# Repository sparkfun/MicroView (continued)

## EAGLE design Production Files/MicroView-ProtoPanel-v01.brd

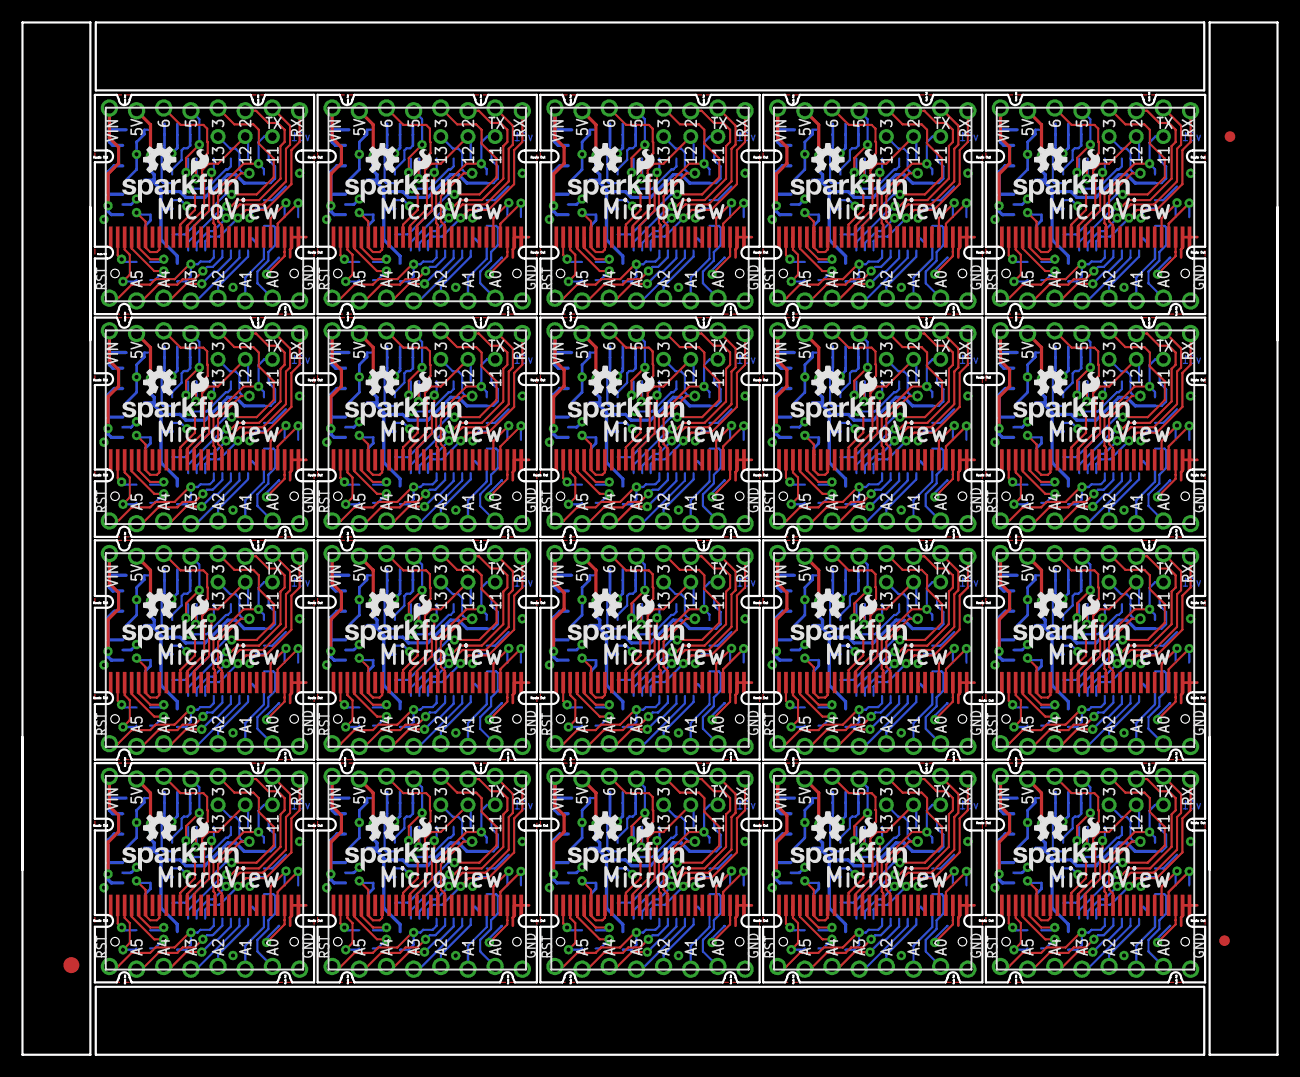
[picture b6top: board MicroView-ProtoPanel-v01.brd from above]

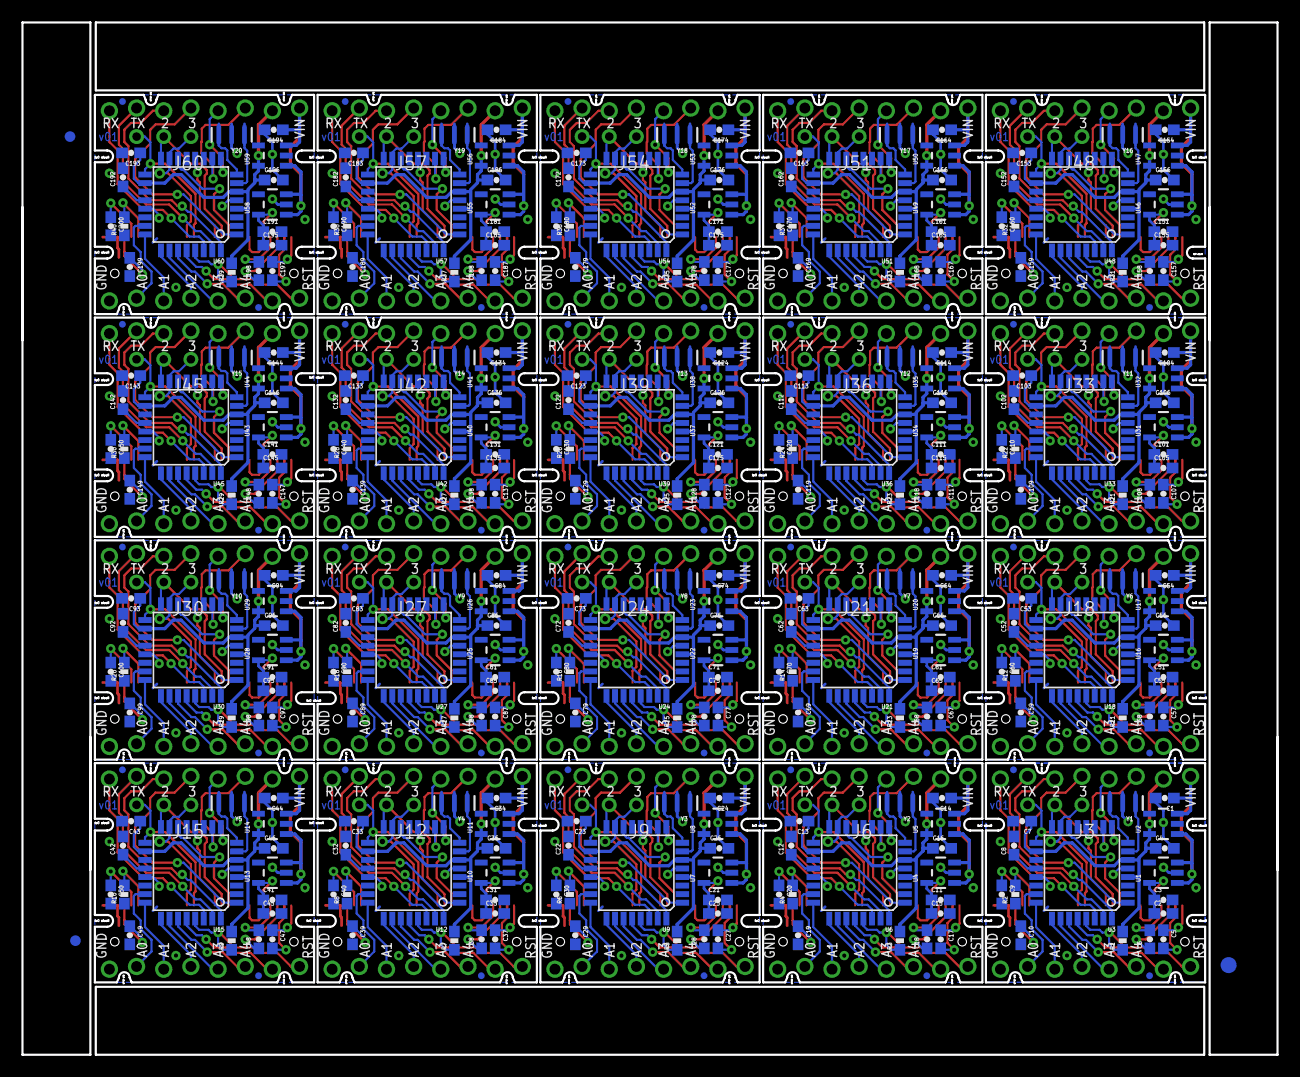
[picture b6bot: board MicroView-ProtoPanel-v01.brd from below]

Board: 2 copper layers, 117.3 x 96.5 mm, 486 parts (383 on the bottom side), 640 nets.

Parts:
C1, C2, C4, C5, C6, C14, C15, C16, C17, C18, C24, C25, C26, C27, C28, C34, C35, C36, C37, C38, C44, C45, C46, C47, C48, C54, C55, C56, C57, C58, C64, C65, C66, C67, C68, C74, C75, C76, C77, C78, C84, C85, C86, C87, C88, C94, C95, C96, C97, C98, C104, C105, C106, C107, C108, C114, C115, C116, C117, C118, C124, C125, C126, C127, C128, C134, C135, C136, C137, C138, C144, C145, C146, C147, C148, C154, C155, C156, C157, C158, C164, C165, C166, C167, C168, C174, C175, C176, C177, C178, C184, C185, C186, C187, C188, C194, C195, C196, C197, C198: 1.0uF; 0603-CAP
C3, C7, C8, C11, C12, C13, C21, C22, C23, C31, C32, C33, C41, C42, C43, C51, C52, C53, C61, C62, C63, C71, C72, C73, C81, C82, C83, C91, C92, C93, C101, C102, C103, C111, C112, C113, C121, C122, C123, C131, C132, C133, C141, C142, C143, C151, C152, C153, C161, C162, C163, C171, C172, C173, C181, C182, C183, C191, C192, C193: 0.1uF; 0603-CAP
C9, C10, C19, C20, C29, C30, C39, C40, C49, C50, C59, C60, C69, C70, C79, C80, C89, C90, C99, C100, C109, C110, C119, C120, C129, C130, C139, C140, C149, C150, C159, C160, C169, C170, C179, C180, C189, C190, C199, C200: 2.2uF; 0603-CAP
E$1, E$2: FIDUCIAL-1.5X3
E$3, E$4, E$5, E$6: FIDUCIAL-1X2
FID1, FID2, FID3, FID4, FID5, FID6, FID7, FID8, FID9, FID10, FID11, FID12, FID13, FID14, FID15, FID16, FID17, FID18, FID19, FID20, FID21, FID22, FID23, FID24, FID25, FID26, FID27, FID28, FID29, FID30, FID31, FID32, FID33, FID34, FID35, FID36, FID37, FID38, FID39, FID40: FIDUCIALUFIDUCIAL; MICRO-FIDUCIAL
J1, J5, J8, J11, J14, J17, J20, J23, J26, J29, J32, J35, J38, J41, J44, J47, J50, J53, J56, J59: OLED_SCREEN; OLED-SCREEN
J2, J4, J7, J10, J13, J16, J19, J22, J25, J28, J31, J34, J37, J40, J43, J46, J49, J52, J55, J58: MICROVIEW-16; MV-DIP16
J3, J6, J9, J12, J15, J18, J21, J24, J27, J30, J33, J36, J39, J42, J45, J48, J51, J54, J57, J60: M03NS_SLIM; 1X03_NS_SLIM
LOGO1, LOGO2, LOGO5, LOGO7, LOGO9, LOGO11, LOGO13, LOGO15, LOGO17, LOGO19, LOGO21, LOGO23, LOGO25, LOGO27, LOGO29, LOGO31, LOGO33, LOGO35, LOGO37, LOGO39: OSHW-LOGOS; OSHW-LOGO-S
LOGO3, LOGO4, LOGO6, LOGO8, LOGO10, LOGO12, LOGO14, LOGO16, LOGO18, LOGO20, LOGO22, LOGO24, LOGO26, LOGO28, LOGO30, LOGO32, LOGO34, LOGO36, LOGO38, LOGO40: SFE_LOGO_NAME_FLAME.1_INCH; SFE_LOGO_NAME_FLAME_.1
OLED1, OLED2, OLED3, OLED4, OLED5, OLED6, OLED7, OLED8, OLED9, OLED10, OLED11, OLED12, OLED13, OLED14, OLED15, OLED16, OLED17, OLED18, OLED19, OLED20: OLED0.66; OLED-0.66-64X48
R1, R3, R5, R7, R9, R11, R13, R15, R17, R19, R21, R23, R25, R27, R29, R31, R33, R35, R37, R39: 10K; 0603-RES
R2, R4, R6, R8, R10, R12, R14, R16, R18, R20, R22, R24, R26, R28, R30, R32, R34, R36, R38, R40: 390k; 0603-RES
U1, U4, U7, U10, U13, U16, U19, U22, U25, U28, U31, U34, U37, U40, U43, U46, U49, U52, U55, U58: MIC5205 3.3V; SOT23-5
U2, U5, U8, U11, U14, U17, U20, U23, U26, U29, U32, U35, U38, U41, U44, U47, U50, U53, U56, U59: SPX3819M5-L-5-0; SOT23-5
U3, U6, U9, U12, U15, U18, U21, U24, U27, U30, U33, U36, U39, U42, U45, U48, U51, U54, U57, U60: ATMEGA328P; TQFP32-08
Y1, Y2, Y3, Y4, Y5, Y6, Y7, Y8, Y9, Y10, Y11, Y12, Y13, Y14, Y15, Y16, Y17, Y18, Y19, Y20: 16MHz; RESONATOR-SMD

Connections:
3.3V: C2.1, C3.1, OLED1.6, OLED1.8, U1.5
3.3V1: C11.1, C15.1, OLED2.6, OLED2.8, U4.5
3.3V2: C21.1, C25.1, OLED3.6, OLED3.8, U7.5
3.3V3: C31.1, C35.1, OLED4.6, OLED4.8, U10.5
3.3V4: C41.1, C45.1, OLED5.6, OLED5.8, U13.5
3.3V5: C51.1, C55.1, OLED6.6, OLED6.8, U16.5
3.3V6: C61.1, C65.1, OLED7.6, OLED7.8, U19.5
3.3V7: C71.1, C75.1, OLED8.6, OLED8.8, U22.5
3.3V8: C81.1, C85.1, OLED9.6, OLED9.8, U25.5
3.3V9: C91.1, C95.1, OLED10.6, OLED10.8, U28.5
3.3V10: C101.1, C105.1, OLED11.6, OLED11.8, U31.5
3.3V11: C111.1, C115.1, OLED12.6, OLED12.8, U34.5
3.3V12: C121.1, C125.1, OLED13.6, OLED13.8, U37.5
3.3V13: C131.1, C135.1, OLED14.6, OLED14.8, U40.5
3.3V14: C141.1, C145.1, OLED15.6, OLED15.8, U43.5
3.3V15: C151.1, C155.1, OLED16.6, OLED16.8, U46.5
3.3V16: C161.1, C165.1, OLED17.6, OLED17.8, U49.5
3.3V17: C171.1, C175.1, OLED18.6, OLED18.8, U52.5
3.3V18: C181.1, C185.1, OLED19.6, OLED19.8, U55.5
3.3V19: C191.1, C195.1, OLED20.6, OLED20.8, U58.5
5V: C4.1, C7.1, J2.15, R1.2, U2.5, U3.4, U3.6, U3.18
5V1: C13.1, C16.1, J4.15, R3.2, U5.5, U6.4, U6.6, U6.18
5V2: C23.1, C26.1, J7.15, R5.2, U8.5, U9.4, U9.6, U9.18
5V3: C33.1, C36.1, J10.15, R7.2, U11.5, U12.4, U12.6, U12.18
5V4: C43.1, C46.1, J13.15, R9.2, U14.5, U15.4, U15.6, U15.18
5V5: C53.1, C56.1, J16.15, R11.2, U17.5, U18.4, U18.6, U18.18
5V6: C63.1, C66.1, J19.15, R13.2, U20.5, U21.4, U21.6, U21.18
5V7: C73.1, C76.1, J22.15, R15.2, U23.5, U24.4, U24.6, U24.18
5V8: C83.1, C86.1, J25.15, R17.2, U26.5, U27.4, U27.6, U27.18
5V9: C93.1, C96.1, J28.15, R19.2, U29.5, U30.4, U30.6, U30.18
5V10: C103.1, C106.1, J31.15, R21.2, U32.5, U33.4, U33.6, U33.18
5V11: C113.1, C116.1, J34.15, R23.2, U35.5, U36.4, U36.6, U36.18
5V12: C123.1, C126.1, J37.15, R25.2, U38.5, U39.4, U39.6, U39.18
5V13: C133.1, C136.1, J40.15, R27.2, U41.5, U42.4, U42.6, U42.18
5V14: C143.1, C146.1, J43.15, R29.2, U44.5, U45.4, U45.6, U45.18
5V15: C153.1, C156.1, J46.15, R31.2, U47.5, U48.4, U48.6, U48.18
5V16: C163.1, C166.1, J49.15, R33.2, U50.5, U51.4, U51.6, U51.18
5V17: C173.1, C176.1, J52.15, R35.2, U53.5, U54.4, U54.6, U54.18
5V18: C183.1, C186.1, J55.15, R37.2, U56.5, U57.4, U57.6, U57.18
5V19: C193.1, C196.1, J58.15, R39.2, U59.5, U60.4, U60.6, U60.18
A0: J2.7, U3.23
A1: J2.6, U3.24
A2: J2.5, U3.25
A3: J2.4, U3.26
A4: J2.3, U3.27
A5: J2.2, U3.28
A6: J4.7, U6.23
A7: J4.6, U6.24
A8: J4.5, U6.25
A9: J4.4, U6.26
A10: J4.3, U6.27
A11: J4.2, U6.28
A12: J7.7, U9.23
A13: J7.6, U9.24
A14: J7.5, U9.25
A15: J7.4, U9.26
A16: J7.3, U9.27
A17: J7.2, U9.28
A18: J10.7, U12.23
A19: J10.6, U12.24
A20: J10.5, U12.25
A21: J10.4, U12.26
A22: J10.3, U12.27
A23: J10.2, U12.28
A24: J13.7, U15.23
A25: J13.6, U15.24
A26: J13.5, U15.25
A27: J13.4, U15.26
A28: J13.3, U15.27
A29: J13.2, U15.28
A30: J16.7, U18.23
A31: J16.6, U18.24
A32: J16.5, U18.25
A33: J16.4, U18.26
A34: J16.3, U18.27
A35: J16.2, U18.28
A36: J19.7, U21.23
A37: J19.6, U21.24
A38: J19.5, U21.25
A39: J19.4, U21.26
A40: J19.3, U21.27
A41: J19.2, U21.28
A42: J22.7, U24.23
A43: J22.6, U24.24
A44: J22.5, U24.25
A45: J22.4, U24.26
A46: J22.3, U24.27
A47: J22.2, U24.28
A48: J25.7, U27.23
A49: J25.6, U27.24
A50: J25.5, U27.25
A51: J25.4, U27.26
A52: J25.3, U27.27
A53: J25.2, U27.28
A54: J28.7, U30.23
A55: J28.6, U30.24
A56: J28.5, U30.25
A57: J28.4, U30.26
A58: J28.3, U30.27
A59: J28.2, U30.28
A60: J31.7, U33.23
A61: J31.6, U33.24
A62: J31.5, U33.25
A63: J31.4, U33.26
A64: J31.3, U33.27
A65: J31.2, U33.28
A66: J34.7, U36.23
A67: J34.6, U36.24
A68: J34.5, U36.25
A69: J34.4, U36.26
A70: J34.3, U36.27
A71: J34.2, U36.28
A72: J37.7, U39.23
A73: J37.6, U39.24
A74: J37.5, U39.25
A75: J37.4, U39.26
A76: J37.3, U39.27
A77: J37.2, U39.28
A78: J40.7, U42.23
A79: J40.6, U42.24
A80: J40.5, U42.25
A81: J40.4, U42.26
A82: J40.3, U42.27
A83: J40.2, U42.28
A84: J43.7, U45.23
A85: J43.6, U45.24
A86: J43.5, U45.25
A87: J43.4, U45.26
A88: J43.3, U45.27
A89: J43.2, U45.28
A90: J46.7, U48.23
A91: J46.6, U48.24
A92: J46.5, U48.25
A93: J46.4, U48.26
A94: J46.3, U48.27
A95: J46.2, U48.28
A96: J49.7, U51.23
A97: J49.6, U51.24
A98: J49.5, U51.25
A99: J49.4, U51.26
A100: J49.3, U51.27
A101: J49.2, U51.28
A102: J52.7, U54.23
A103: J52.6, U54.24
A104: J52.5, U54.25
A105: J52.4, U54.26
A106: J52.3, U54.27
A107: J52.2, U54.28
A108: J55.7, U57.23
A109: J55.6, U57.24
A110: J55.5, U57.25
A111: J55.4, U57.26
A112: J55.3, U57.27
A113: J55.2, U57.28
A114: J58.7, U60.23
A115: J58.6, U60.24
A116: J58.5, U60.25
A117: J58.4, U60.26
A118: J58.3, U60.27
A119: J58.2, U60.28
C1N: C6.2, OLED1.5
C1N1: C18.2, OLED2.5
C1N2: C28.2, OLED3.5
C1N3: C38.2, OLED4.5
C1N4: C48.2, OLED5.5
C1N5: C58.2, OLED6.5
C1N6: C68.2, OLED7.5
C1N7: C78.2, OLED8.5
C1N8: C88.2, OLED9.5
C1N9: C98.2, OLED10.5
C1N10: C108.2, OLED11.5
C1N11: C118.2, OLED12.5
C1N12: C128.2, OLED13.5
C1N13: C138.2, OLED14.5
C1N14: C148.2, OLED15.5
C1N15: C158.2, OLED16.5
C1N16: C168.2, OLED17.5
C1N17: C178.2, OLED18.5
C1N18: C188.2, OLED19.5
C1N19: C198.2, OLED20.5
C1P: C6.1, OLED1.4
C1P1: C18.1, OLED2.4
C1P2: C28.1, OLED3.4
C1P3: C38.1, OLED4.4
C1P4: C48.1, OLED5.4
C1P5: C58.1, OLED6.4
C1P6: C68.1, OLED7.4
C1P7: C78.1, OLED8.4
C1P8: C88.1, OLED9.4
C1P9: C98.1, OLED10.4
C1P10: C108.1, OLED11.4
C1P11: C118.1, OLED12.4
C1P12: C128.1, OLED13.4
C1P13: C138.1, OLED14.4
C1P14: C148.1, OLED15.4
C1P15: C158.1, OLED16.4
C1P16: C168.1, OLED17.4
C1P17: C178.1, OLED18.4
C1P18: C188.1, OLED19.4
C1P19: C198.1, OLED20.4
C2N: C5.2, OLED1.3
C2N1: C17.2, OLED2.3
C2N2: C27.2, OLED3.3
C2N3: C37.2, OLED4.3
C2N4: C47.2, OLED5.3
C2N5: C57.2, OLED6.3
C2N6: C67.2, OLED7.3
C2N7: C77.2, OLED8.3
C2N8: C87.2, OLED9.3
C2N9: C97.2, OLED10.3
C2N10: C107.2, OLED11.3
C2N11: C117.2, OLED12.3
C2N12: C127.2, OLED13.3
C2N13: C137.2, OLED14.3
C2N14: C147.2, OLED15.3
C2N15: C157.2, OLED16.3
C2N16: C167.2, OLED17.3
C2N17: C177.2, OLED18.3
C2N18: C187.2, OLED19.3
C2N19: C197.2, OLED20.3
C2P: C5.1, OLED1.2
C2P1: C17.1, OLED2.2
C2P2: C27.1, OLED3.2
C2P3: C37.1, OLED4.2
C2P4: C47.1, OLED5.2
C2P5: C57.1, OLED6.2
C2P6: C67.1, OLED7.2
C2P7: C77.1, OLED8.2
C2P8: C87.1, OLED9.2
C2P9: C97.1, OLED10.2
C2P10: C107.1, OLED11.2
C2P11: C117.1, OLED12.2
C2P12: C127.1, OLED13.2
C2P13: C137.1, OLED14.2
C2P14: C147.1, OLED15.2
C2P15: C157.1, OLED16.2
C2P16: C167.1, OLED17.2
C2P17: C177.1, OLED18.2
C2P18: C187.1, OLED19.2
C2P19: C197.1, OLED20.2
D1: J4.11, U6.32
D2: J2.11, U3.32
D3: J2.12, U3.1
D4: J4.12, U6.1
D5: J2.13, U3.9
D6: J2.14, U3.10
D7: J4.13, U6.9
D8: J4.14, U6.10
D8/D!C!: OLED1.13, U3.12
D8/D!C!1: OLED2.13, U6.12
D8/D!C!2: OLED3.13, U9.12
D8/D!C!3: OLED4.13, U12.12
D8/D!C!4: OLED5.13, U15.12
D8/D!C!5: OLED6.13, U18.12
D8/D!C!6: OLED7.13, U21.12
D8/D!C!7: OLED8.13, U24.12
D8/D!C!8: OLED9.13, U27.12
D8/D!C!9: OLED10.13, U30.12
D8/D!C!10: OLED11.13, U33.12
D8/D!C!11: OLED12.13, U36.12
D8/D!C!12: OLED13.13, U39.12
D8/D!C!13: OLED14.13, U42.12
D8/D!C!14: OLED15.13, U45.12
D8/D!C!15: OLED16.13, U48.12
D8/D!C!16: OLED17.13, U51.12
D8/D!C!17: OLED18.13, U54.12
D8/D!C!18: OLED19.13, U57.12
D8/D!C!19: OLED20.13, U60.12
D9: J7.11, U9.32
D10: J7.12, U9.1
D10/SS: OLED1.11, U3.14
D10/SS1: OLED2.11, U6.14
D10/SS2: OLED3.11, U9.14
D10/SS3: OLED4.11, U12.14
D10/SS4: OLED5.11, U15.14
D10/SS5: OLED6.11, U18.14
D10/SS6: OLED7.11, U21.14
D10/SS7: OLED8.11, U24.14
D10/SS8: OLED9.11, U27.14
D10/SS9: OLED10.11, U30.14
D10/SS10: OLED11.11, U33.14
D10/SS11: OLED12.11, U36.14
D10/SS12: OLED13.11, U39.14
D10/SS13: OLED14.11, U42.14
D10/SS14: OLED15.11, U45.14
D10/SS15: OLED16.11, U48.14
D10/SS16: OLED17.11, U51.14
D10/SS17: OLED18.11, U54.14
D10/SS18: OLED19.11, U57.14
D10/SS19: OLED20.11, U60.14
D11: J7.13, U9.9
D11/MOSI: J3.1, OLED1.17, U3.15
D11/MOSI1: J6.1, OLED2.17, U6.15
D11/MOSI2: J9.1, OLED3.17, U9.15
D11/MOSI3: J12.1, OLED4.17, U12.15
D11/MOSI4: J15.1, OLED5.17, U15.15
D11/MOSI5: J18.1, OLED6.17, U18.15
D11/MOSI6: J21.1, OLED7.17, U21.15
D11/MOSI7: J24.1, OLED8.17, U24.15
D11/MOSI8: J27.1, OLED9.17, U27.15
D11/MOSI9: J30.1, OLED10.17, U30.15
D11/MOSI10: J33.1, OLED11.17, U33.15
D11/MOSI11: J36.1, OLED12.17, U36.15
D11/MOSI12: J39.1, OLED13.17, U39.15
D11/MOSI13: J42.1, OLED14.17, U42.15
D11/MOSI14: J45.1, OLED15.17, U45.15
D11/MOSI15: J48.1, OLED16.17, U48.15
D11/MOSI16: J51.1, OLED17.17, U51.15
D11/MOSI17: J54.1, OLED18.17, U54.15
D11/MOSI18: J57.1, OLED19.17, U57.15
D11/MOSI19: J60.1, OLED20.17, U60.15
D12: J7.14, U9.10
D12/MISO: J3.2, OLED1.12, U3.16
D12/MISO1: J6.2, OLED2.12, U6.16
D12/MISO2: J9.2, OLED3.12, U9.16
D12/MISO3: J12.2, OLED4.12, U12.16
D12/MISO4: J15.2, OLED5.12, U15.16
D12/MISO5: J18.2, OLED6.12, U18.16
D12/MISO6: J21.2, OLED7.12, U21.16
D12/MISO7: J24.2, OLED8.12, U24.16
D12/MISO8: J27.2, OLED9.12, U27.16
D12/MISO9: J30.2, OLED10.12, U30.16
D12/MISO10: J33.2, OLED11.12, U33.16
D12/MISO11: J36.2, OLED12.12, U36.16
D12/MISO12: J39.2, OLED13.12, U39.16
D12/MISO13: J42.2, OLED14.12, U42.16
D12/MISO14: J45.2, OLED15.12, U45.16
D12/MISO15: J48.2, OLED16.12, U48.16
D12/MISO16: J51.2, OLED17.12, U51.16
D12/MISO17: J54.2, OLED18.12, U54.16
D12/MISO18: J57.2, OLED19.12, U57.16
D12/MISO19: J60.2, OLED20.12, U60.16
D13: J10.11, U12.32
D13/SCK: J3.3, OLED1.16, U3.17
D13/SCK1: J6.3, OLED2.16, U6.17
D13/SCK2: J9.3, OLED3.16, U9.17
D13/SCK3: J12.3, OLED4.16, U12.17
D13/SCK4: J15.3, OLED5.16, U15.17
D13/SCK5: J18.3, OLED6.16, U18.17
D13/SCK6: J21.3, OLED7.16, U21.17
D13/SCK7: J24.3, OLED8.16, U24.17
D13/SCK8: J27.3, OLED9.16, U27.17
D13/SCK9: J30.3, OLED10.16, U30.17
D13/SCK10: J33.3, OLED11.16, U33.17
D13/SCK11: J36.3, OLED12.16, U36.17
D13/SCK12: J39.3, OLED13.16, U39.17
D13/SCK13: J42.3, OLED14.16, U42.17
D13/SCK14: J45.3, OLED15.16, U45.17
D13/SCK15: J48.3, OLED16.16, U48.17
D13/SCK16: J51.3, OLED17.16, U51.17
D13/SCK17: J54.3, OLED18.16, U54.17
D13/SCK18: J57.3, OLED19.16, U57.17
D13/SCK19: J60.3, OLED20.16, U60.17
D14: J10.12, U12.1
D15: J10.13, U12.9
D16: J10.14, U12.10
D17: J13.11, U15.32
D18: J13.12, U15.1
D19: J13.13, U15.9
D20: J13.14, U15.10
D21: J16.11, U18.32
D22: J16.12, U18.1
D23: J16.13, U18.9
D24: J16.14, U18.10
D25: J19.11, U21.32
D26: J19.12, U21.1
D27: J19.13, U21.9
D28: J19.14, U21.10
D29: J22.11, U24.32
D30: J22.12, U24.1
D31: J22.13, U24.9
D32: J22.14, U24.10
D33: J25.11, U27.32
D34: J25.12, U27.1
D35: J25.13, U27.9
D36: J25.14, U27.10
D37: J28.11, U30.32
D38: J28.12, U30.1
D39: J28.13, U30.9
D40: J28.14, U30.10
D41: J31.11, U33.32
D42: J31.12, U33.1
D43: J31.13, U33.9
D44: J31.14, U33.10
D45: J34.11, U36.32
D46: J34.12, U36.1
D47: J34.13, U36.9
D48: J34.14, U36.10
D49: J37.11, U39.32
D50: J37.12, U39.1
D51: J37.13, U39.9
D52: J37.14, U39.10
D53: J40.11, U42.32
D54: J40.12, U42.1
D55: J40.13, U42.9
D56: J40.14, U42.10
D57: J43.11, U45.32
D58: J43.12, U45.1
D59: J43.13, U45.9
D60: J43.14, U45.10
D61: J46.11, U48.32
D62: J46.12, U48.1
D63: J46.13, U48.9
D64: J46.14, U48.10
D65: J49.11, U51.32
D66: J49.12, U51.1
D67: J49.13, U51.9
D68: J49.14, U51.10
D69: J52.11, U54.32
D70: J52.12, U54.1
D71: J52.13, U54.9
D72: J52.14, U54.10
D73: J55.11, U57.32
D74: J55.12, U57.1
D75: J55.13, U57.9
D76: J55.14, U57.10
D77: J58.11, U60.32
D78: J58.12, U60.1
D79: J58.13, U60.9
D80: J58.14, U60.10
GND: C1.2, C2.2, C3.2, C4.2, C7.2, C8.2, C9.2, C10.2, J2.8, OLED1.1, OLED1.7, OLED1.9, OLED1.10, OLED1.27, OLED1.28, R2.1, U1.2, U2.2, U3.3, U3.5, U3.21, Y1.2
GND1: C11.2, C12.2, C13.2, C14.2, C15.2, C16.2, C19.2, C20.2, J4.8, OLED2.1, OLED2.7, OLED2.9, OLED2.10, OLED2.27, OLED2.28, R4.1, U4.2, U5.2, U6.3, U6.5, U6.21, Y2.2
GND2: C21.2, C22.2, C23.2, C24.2, C25.2, C26.2, C29.2, C30.2, J7.8, OLED3.1, OLED3.7, OLED3.9, OLED3.10, OLED3.27, OLED3.28, R6.1, U7.2, U8.2, U9.3, U9.5, U9.21, Y3.2
GND3: C31.2, C32.2, C33.2, C34.2, C35.2, C36.2, C39.2, C40.2, J10.8, OLED4.1, OLED4.7, OLED4.9, OLED4.10, OLED4.27, OLED4.28, R8.1, U10.2, U11.2, U12.3, U12.5, U12.21, Y4.2
GND4: C41.2, C42.2, C43.2, C44.2, C45.2, C46.2, C49.2, C50.2, J13.8, OLED5.1, OLED5.7, OLED5.9, OLED5.10, OLED5.27, OLED5.28, R10.1, U13.2, U14.2, U15.3, U15.5, U15.21, Y5.2
GND5: C51.2, C52.2, C53.2, C54.2, C55.2, C56.2, C59.2, C60.2, J16.8, OLED6.1, OLED6.7, OLED6.9, OLED6.10, OLED6.27, OLED6.28, R12.1, U16.2, U17.2, U18.3, U18.5, U18.21, Y6.2
GND6: C61.2, C62.2, C63.2, C64.2, C65.2, C66.2, C69.2, C70.2, J19.8, OLED7.1, OLED7.7, OLED7.9, OLED7.10, OLED7.27, OLED7.28, R14.1, U19.2, U20.2, U21.3, U21.5, U21.21, Y7.2
GND7: C71.2, C72.2, C73.2, C74.2, C75.2, C76.2, C79.2, C80.2, J22.8, OLED8.1, OLED8.7, OLED8.9, OLED8.10, OLED8.27, OLED8.28, R16.1, U22.2, U23.2, U24.3, U24.5, U24.21, Y8.2
GND8: C81.2, C82.2, C83.2, C84.2, C85.2, C86.2, C89.2, C90.2, J25.8, OLED9.1, OLED9.7, OLED9.9, OLED9.10, OLED9.27, OLED9.28, R18.1, U25.2, U26.2, U27.3, U27.5, U27.21, Y9.2
GND9: C91.2, C92.2, C93.2, C94.2, C95.2, C96.2, C99.2, C100.2, J28.8, OLED10.1, OLED10.7, OLED10.9, OLED10.10, OLED10.27, OLED10.28, R20.1, U28.2, U29.2, U30.3, U30.5, U30.21, Y10.2
GND10: C101.2, C102.2, C103.2, C104.2, C105.2, C106.2, C109.2, C110.2, J31.8, OLED11.1, OLED11.7, OLED11.9, OLED11.10, OLED11.27, OLED11.28, R22.1, U31.2, U32.2, U33.3, U33.5, U33.21, Y11.2
GND11: C111.2, C112.2, C113.2, C114.2, C115.2, C116.2, C119.2, C120.2, J34.8, OLED12.1, OLED12.7, OLED12.9, OLED12.10, OLED12.27, OLED12.28, R24.1, U34.2, U35.2, U36.3, U36.5, U36.21, Y12.2
GND12: C121.2, C122.2, C123.2, C124.2, C125.2, C126.2, C129.2, C130.2, J37.8, OLED13.1, OLED13.7, OLED13.9, OLED13.10, OLED13.27, OLED13.28, R26.1, U37.2, U38.2, U39.3, U39.5, U39.21, Y13.2
GND13: C131.2, C132.2, C133.2, C134.2, C135.2, C136.2, C139.2, C140.2, J40.8, OLED14.1, OLED14.7, OLED14.9, OLED14.10, OLED14.27, OLED14.28, R28.1, U40.2, U41.2, U42.3, U42.5, U42.21, Y14.2
GND14: C141.2, C142.2, C143.2, C144.2, C145.2, C146.2, C149.2, C150.2, J43.8, OLED15.1, OLED15.7, OLED15.9, OLED15.10, OLED15.27, OLED15.28, R30.1, U43.2, U44.2, U45.3, U45.5, U45.21, Y15.2
GND15: C151.2, C152.2, C153.2, C154.2, C155.2, C156.2, C159.2, C160.2, J46.8, OLED16.1, OLED16.7, OLED16.9, OLED16.10, OLED16.27, OLED16.28, R32.1, U46.2, U47.2, U48.3, U48.5, U48.21, Y16.2
GND16: C161.2, C162.2, C163.2, C164.2, C165.2, C166.2, C169.2, C170.2, J49.8, OLED17.1, OLED17.7, OLED17.9, OLED17.10, OLED17.27, OLED17.28, R34.1, U49.2, U50.2, U51.3, U51.5, U51.21, Y17.2
GND17: C171.2, C172.2, C173.2, C174.2, C175.2, C176.2, C179.2, C180.2, J52.8, OLED18.1, OLED18.7, OLED18.9, OLED18.10, OLED18.27, OLED18.28, R36.1, U52.2, U53.2, U54.3, U54.5, U54.21, Y18.2
GND18: C181.2, C182.2, C183.2, C184.2, C185.2, C186.2, C189.2, C190.2, J55.8, OLED19.1, OLED19.7, OLED19.9, OLED19.10, OLED19.27, OLED19.28, R38.1, U55.2, U56.2, U57.3, U57.5, U57.21, Y19.2
GND19: C191.2, C192.2, C193.2, C194.2, C195.2, C196.2, C199.2, C200.2, J58.8, OLED20.1, OLED20.7, OLED20.9, OLED20.10, OLED20.27, OLED20.28, R40.1, U58.2, U59.2, U60.3, U60.5, U60.21, Y20.2
unnamed: C10.1, OLED1.26
unnamed: C9.1, OLED1.25
unnamed: OLED1.24, R2.2
unnamed: C19.1, OLED2.26
unnamed: C20.1, OLED2.25
unnamed: OLED2.24, R4.2
unnamed: U6.7, Y2.1
unnamed: U3.7, Y1.1
unnamed: U3.8, Y1.3
unnamed: C8.1, U3.20
unnamed: U6.8, Y2.3
unnamed: C12.1, U6.20
unnamed: C29.1, OLED3.26
unnamed: C30.1, OLED3.25
unnamed: OLED3.24, R6.2
unnamed: U9.7, Y3.1
unnamed: U9.8, Y3.3
unnamed: C22.1, U9.20
unnamed: C39.1, OLED4.26
unnamed: C40.1, OLED4.25
unnamed: OLED4.24, R8.2
unnamed: U12.7, Y4.1
unnamed: U12.8, Y4.3
unnamed: C32.1, U12.20
unnamed: C49.1, OLED5.26
unnamed: C50.1, OLED5.25
unnamed: OLED5.24, R10.2
unnamed: U15.7, Y5.1
unnamed: U15.8, Y5.3
unnamed: C42.1, U15.20
unnamed: C59.1, OLED6.26
unnamed: C60.1, OLED6.25
unnamed: OLED6.24, R12.2
unnamed: U18.7, Y6.1
unnamed: U18.8, Y6.3
unnamed: C52.1, U18.20
unnamed: C69.1, OLED7.26
unnamed: C70.1, OLED7.25
unnamed: OLED7.24, R14.2
unnamed: U21.7, Y7.1
unnamed: U21.8, Y7.3
unnamed: C62.1, U21.20
unnamed: C79.1, OLED8.26
unnamed: C80.1, OLED8.25
unnamed: OLED8.24, R16.2
unnamed: U24.7, Y8.1
unnamed: U24.8, Y8.3
unnamed: C72.1, U24.20
unnamed: C89.1, OLED9.26
unnamed: C90.1, OLED9.25
unnamed: OLED9.24, R18.2
unnamed: U27.7, Y9.1
unnamed: U27.8, Y9.3
unnamed: C82.1, U27.20
unnamed: C99.1, OLED10.26
unnamed: C100.1, OLED10.25
unnamed: OLED10.24, R20.2
unnamed: U30.7, Y10.1
unnamed: U30.8, Y10.3
unnamed: C92.1, U30.20
unnamed: C109.1, OLED11.26
unnamed: C110.1, OLED11.25
unnamed: OLED11.24, R22.2
unnamed: U33.7, Y11.1
unnamed: U33.8, Y11.3
unnamed: C102.1, U33.20
unnamed: C119.1, OLED12.26
unnamed: C120.1, OLED12.25
unnamed: OLED12.24, R24.2
unnamed: U36.7, Y12.1
unnamed: U36.8, Y12.3
unnamed: C112.1, U36.20
unnamed: C129.1, OLED13.26
unnamed: C130.1, OLED13.25
unnamed: OLED13.24, R26.2
unnamed: U39.7, Y13.1
unnamed: U39.8, Y13.3
unnamed: C122.1, U39.20
unnamed: C139.1, OLED14.26
unnamed: C140.1, OLED14.25
unnamed: OLED14.24, R28.2
unnamed: U42.7, Y14.1
unnamed: U42.8, Y14.3
unnamed: C132.1, U42.20
unnamed: C149.1, OLED15.26
unnamed: C150.1, OLED15.25
unnamed: OLED15.24, R30.2
unnamed: U45.7, Y15.1
unnamed: U45.8, Y15.3
unnamed: C142.1, U45.20
unnamed: C159.1, OLED16.26
unnamed: C160.1, OLED16.25
unnamed: OLED16.24, R32.2
unnamed: U48.7, Y16.1
unnamed: U48.8, Y16.3
unnamed: C152.1, U48.20
unnamed: C169.1, OLED17.26
unnamed: C170.1, OLED17.25
unnamed: OLED17.24, R34.2
unnamed: U51.7, Y17.1
unnamed: U51.8, Y17.3
unnamed: C162.1, U51.20
unnamed: C179.1, OLED18.26
unnamed: C180.1, OLED18.25
unnamed: OLED18.24, R36.2
unnamed: U54.7, Y18.1
unnamed: U54.8, Y18.3
unnamed: C172.1, U54.20
unnamed: C189.1, OLED19.26
unnamed: C190.1, OLED19.25
unnamed: OLED19.24, R38.2
unnamed: U57.7, Y19.1
unnamed: U57.8, Y19.3
unnamed: C182.1, U57.20
unnamed: C199.1, OLED20.26
unnamed: C200.1, OLED20.25
unnamed: OLED20.24, R40.2
unnamed: U60.7, Y20.1
unnamed: U60.8, Y20.3
unnamed: C192.1, U60.20
RESET: J2.1, R1.1, U3.29
RESET1: J4.1, R3.1, U6.29
RESET2: J7.1, R5.1, U9.29
RESET3: J10.1, R7.1, U12.29
RESET4: J13.1, R9.1, U15.29
RESET5: J16.1, R11.1, U18.29
RESET6: J19.1, R13.1, U21.29
RESET7: J22.1, R15.1, U24.29
RESET8: J25.1, R17.1, U27.29
RESET9: J28.1, R19.1, U30.29
RESET10: J31.1, R21.1, U33.29
RESET11: J34.1, R23.1, U36.29
RESET12: J37.1, R25.1, U39.29
RESET13: J40.1, R27.1, U42.29
RESET14: J43.1, R29.1, U45.29
RESET15: J46.1, R31.1, U48.29
RESET16: J49.1, R33.1, U51.29
RESET17: J52.1, R35.1, U54.29
RESET18: J55.1, R37.1, U57.29
RESET19: J58.1, R39.1, U60.29
RXD: J2.9, U3.30
RXD1: J4.9, U6.30
RXD2: J7.9, U9.30
RXD3: J10.9, U12.30
RXD4: J13.9, U15.30
RXD5: J16.9, U18.30
RXD6: J19.9, U21.30
RXD7: J22.9, U24.30
RXD8: J25.9, U27.30
RXD9: J28.9, U30.30
RXD10: J31.9, U33.30
RXD11: J34.9, U36.30
RXD12: J37.9, U39.30
RXD13: J40.9, U42.30
RXD14: J43.9, U45.30
RXD15: J46.9, U48.30
RXD16: J49.9, U51.30
RXD17: J52.9, U54.30
RXD18: J55.9, U57.30
RXD19: J58.9, U60.30
TXD: J2.10, U3.31
TXD1: J4.10, U6.31
TXD2: J7.10, U9.31
TXD3: J10.10, U12.31
TXD4: J13.10, U15.31
TXD5: J16.10, U18.31
TXD6: J19.10, U21.31
TXD7: J22.10, U24.31
TXD8: J25.10, U27.31
TXD9: J28.10, U30.31
TXD10: J31.10, U33.31
TXD11: J34.10, U36.31
TXD12: J37.10, U39.31
TXD13: J40.10, U42.31
TXD14: J43.10, U45.31
TXD15: J46.10, U48.31
TXD16: J49.10, U51.31
TXD17: J52.10, U54.31
TXD18: J55.10, U57.31
TXD19: J58.10, U60.31
VIN: C1.1, J2.16, U1.1, U1.3, U2.1, U2.3
VIN1: C14.1, J4.16, U4.1, U4.3, U5.1, U5.3
VIN2: C24.1, J7.16, U7.1, U7.3, U8.1, U8.3
VIN3: C34.1, J10.16, U10.1, U10.3, U11.1, U11.3
VIN4: C44.1, J13.16, U13.1, U13.3, U14.1, U14.3
VIN5: C54.1, J16.16, U16.1, U16.3, U17.1, U17.3
VIN6: C64.1, J19.16, U19.1, U19.3, U20.1, U20.3
VIN7: C74.1, J22.16, U22.1, U22.3, U23.1, U23.3
VIN8: C84.1, J25.16, U25.1, U25.3, U26.1, U26.3
VIN9: C94.1, J28.16, U28.1, U28.3, U29.1, U29.3
VIN10: C104.1, J31.16, U31.1, U31.3, U32.1, U32.3
VIN11: C114.1, J34.16, U34.1, U34.3, U35.1, U35.3
VIN12: C124.1, J37.16, U37.1, U37.3, U38.1, U38.3
VIN13: C134.1, J40.16, U40.1, U40.3, U41.1, U41.3
VIN14: C144.1, J43.16, U43.1, U43.3, U44.1, U44.3
VIN15: C154.1, J46.16, U46.1, U46.3, U47.1, U47.3
VIN16: C164.1, J49.16, U49.1, U49.3, U50.1, U50.3
VIN17: C174.1, J52.16, U52.1, U52.3, U53.1, U53.3
VIN18: C184.1, J55.16, U55.1, U55.3, U56.1, U56.3
VIN19: C194.1, J58.16, U58.1, U58.3, U59.1, U59.3

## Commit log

2014-03-11 Initial commit of hardware files
2014-03-11 Revamping file names
2014-03-11 Adding fids to both boards
2014-03-11 Staggering/increasing drill on headers
    Also spacing out resistors, increasing header fp on MicroViewUSB.
2014-03-12 Updating r's and c's on USB board to prod. parts
    Also rearranging some silk and traces.
2014-03-12 Moving labels on USB board up a bit
    They're probably still going to be overlapped by the header, but this'll
    help a bit.
2014-03-12 Created proto panel v01
2014-04-14 Microview v02 -- new resistors and 3.3Vreg change
    * Added pull-down resistor to OLED Reset. Also moved that pin to D7 on
    the Arduino.
    * Added pull-up resistor to D10/SS.
    * Moved 3.3V regulator input to the 5V line (from Vin)
2014-04-14 Updating version # on schematic (v02)
2014-04-14 Moving USB connector position (MVUSB v02)
    Also added silk to indicate polarity of MV.
2014-04-14 Moving silk indicator on MV-USB a bit.
2014-04-14 Tying 3.3V reg enable to an ATmega pin (D4)
2014-04-17 deleted old proto panel
2014-04-18 Created panels
    Both Giant and regular for small stencil
2014-04-22 Series resistors on MOSI and SCK (v03)
    Limits current into OLED I/O lines. This in conjunction with some code
    changes will help to protect the display from overvoltage.
    This required removing pull-down resistor to RESET and pull-up to SS.
    BUT! You can still program the display, using an ICSP, with the series
    resistors on MOSI and SCK.
2014-04-28 Added windowed upper housing
    Created windowed upper housing for printing in 3d printers with opaque
    material
2014-05-13 Moving some silk around. Production boards (v10).
2014-05-13 created panel v10
2014-05-13 created giant panel
2014-08-10 added MicroView and programmer
2015-01-15 Moving Fritzing files to Fritzing directory
2015-01-15 Moving STL files to Enclosure directory
2015-01-15 Create README.md
    Adding in all repo information and product links.
2015-01-15 Updating README, moving files around to clarify repo structure
2015-03-02 Adding Analog Clock and Pong examples to library.
2015-04-24 Removing un-subtreed Libraries.
2015-04-24 Squashed 'Libraries/Arduino/' content from commit 646247d
    git-subtree-dir: Libraries/Arduino
    git-subtree-split: 646247d149665aa62a394e1d9a87c6b272d31f88
2015-04-24 Libraries subtree, adding Libraries/README.md.
2015-04-28 Squashed 'Libraries/Arduino/' changes from 646247d..f3741f5
    git-subtree-dir: Libraries/Arduino
    git-subtree-split: f3741f5f72b6e2bb11d250358e2f893ce52b99f9
2015-04-28 Updating libraries README with subtree directions
2015-04-28 Fixing production directory name
2016-01-20 Moved Fritzing files to Fritzing Repo
2020-06-09 TimeLib support
    Time.Lib has been deprecated for TimeLib.h. No other changes are required for this example to compile properly.
2025-06-27 Update Circuit8.ino
    Updating link
